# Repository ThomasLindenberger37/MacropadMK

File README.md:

# MacropadMK

MacropadMK is a 12-key macropad built around the Waveshare ESP32-S3-Zero. The
board combines a diode-isolated 4 × 3 keyboard matrix, three USB-C power-entry
options, and two general-purpose JST-SH connections in a compact design.

The PCB is intended for an accessible prototyping workflow: order bare boards,
assemble and validate the first units by hand, then reuse the same LCSC-aware
bill of materials for a later JLCPCB assembly run.

## Design overview

- Controller: ESP32-S3-Zero
- Keyboard: 12 switches arranged as 4 rows × 3 columns
- Isolation: one diode per switch
- Matrix direction: `COL2ROW`
- Supply rails: `BOARD_5V`, `3V3`, and `GND`
- USB-C inputs: the controller connector plus two alternative PCB connectors
- Expansion: two identically pinned 3-position JST-SH connectors

## Keyboard matrix

The switches form a 4-row by 3-column matrix. `ROW1` through `ROW4` are scanned
one at a time by driving the selected row low. `COL1` through `COL3` are inputs,
each held high by an external 10 kΩ pull-up resistor to `3V3`.

Each key is an independent branch:

```text
COLx -> switch -> diode anode -> diode cathode -> ROWx
```

The diode orientation is `COL2ROW`: the cathode, identified by the stripe on the
physical diode, points toward the row line. When a selected row is low and a key
on that row is pressed, its column input is pulled low through the switch and
diode.

| Signal group | Quantity | Scan role | External bias |
| --- | ---: | --- | --- |
| `ROW1`–`ROW4` | 4 | Driven low individually | None |
| `COL1`–`COL3` | 3 | Digital inputs | 10 kΩ to `3V3` per column |

## USB-C power architecture

The ESP32-S3-Zero already has its own USB-C connector. The PCB provides two
additional connector positions as alternative 5 V inputs:

- Horizontal/right-angle: HRO `TYPE-C-31-M-12`
- Vertical/axial: `MC-110LD-L124`, USB 2.0, 16 pins, with THT mounting tabs
- Vertical connector LCSC/JLCPCB part number: `C3039282`

The additional connectors are currently used only for power. They are still
full USB 2.0 connector parts so that the same components and footprints can be
reused in future designs with USB data support.

Each additional receptacle follows these connection rules:

- Tie all VBUS pins of that receptacle together.
- Connect all GND pins to board ground.
- Connect `CC1` to GND through its own 5.1 kΩ resistor.
- Connect `CC2` separately to GND through its own 5.1 kΩ resistor.
- Connect the connector shield to GND.
- Leave `D+`, `D-`, `SBU1`, and `SBU2` unconnected and mark them as no-connect.

Each alternative receptacle feeds the common `BOARD_5V` rail through a separate
solder bridge. `BOARD_5V` connects to the ESP32-S3-Zero 5 V pin. An optional
resettable fuse rated for approximately 1 A can be fitted ahead of the shared
rail.

Place 10 µF bulk capacitance and 100 nF decoupling close to the 5 V input. Route
VBUS with approximately 0.8–1.0 mm wide traces; 0.25 mm traces are not
recommended for a 1 A supply path.

> **Power-source warning:** The board does not provide input OR-ing or reverse-
> current isolation. Only one USB power source may be connected at a time unless
> suitable input decoupling and source isolation are added.

## Additional connectors

The board provides two identically pinned 3-position JST-SH connectors with a
1.0 mm pitch.

- KiCad symbol: `Connector_Generic:Conn_01x03`
- KiCad footprint:
  `Connector_JST:JST_SH_SM03B-SRSS-TB_1x03-1MP_P1.00mm_Horizontal`

| Pin | Signal |
| ---: | --- |
| 1 | `GND` |
| 2 | `3V3` |
| 3 | Signal |

## Sourcing and assembly strategy

Components should use LCSC `C` part numbers wherever practical. The same part
numbers can be used both for loose component orders from LCSC and for JLCPCB
assembly BOM matching.

The intended manufacturing sequence is:

1. Order unassembled prototype PCBs.
2. Hand-assemble and electrically validate the first boards.
3. Resolve ERC/DRC findings and confirm footprints, polarity, and connector
   mechanics.
4. Reuse the validated BOM for a later JLCPCB assembly order.

## Project assets

[Download the schematic as PDF](assets/MacropadMK-schematic.pdf).

Some connector or encoder models may be absent from the rendered 3D preview if
their STEP files are not available locally. This does not affect the Gerber or
drill exports, but mechanical fit must still be checked before ordering.

## Fabrication and documentation exports

The repository contains its KiBot automation directly under `scripts/`. Docker
is required; the scripts use the KiCad 10 KiBot image configured in
`scripts/project.config.yaml`.

Generate the schematic PDF/SVG and the 3D preview:

```bash
./scripts/assets.sh
```

Generate Gerbers, drill files, BOM, placement data, the manufacturer ZIP, and
STEP models:

```bash
./scripts/fabrication.sh
```

Generated manufacturing files are written to `Fabrication/`. The validated
manufacturer archive is `Fabrication/MacropadMK-Gerber_Pack.zip`.

The relevant configuration files are:

- `scripts/project.config.yaml` — project name, KiCad image, PCB thickness, and
  mechanical-hole settings
- `scripts/kibot/config.kibot.yaml` — manufacturing outputs and production
  layers
- `scripts/kibot/kibot_assets.kibot.yaml` — documentation PDF, SVG, and 3D
  render outputs

Always run KiCad ERC and DRC and review the generated Gerbers before submitting
an order. Successful file generation does not imply that the electrical or
mechanical design is production-ready.

## Automated fabrication build

The GitHub Actions fabrication workflow generates manufacturing artifacts when
changes are pushed to the repository:

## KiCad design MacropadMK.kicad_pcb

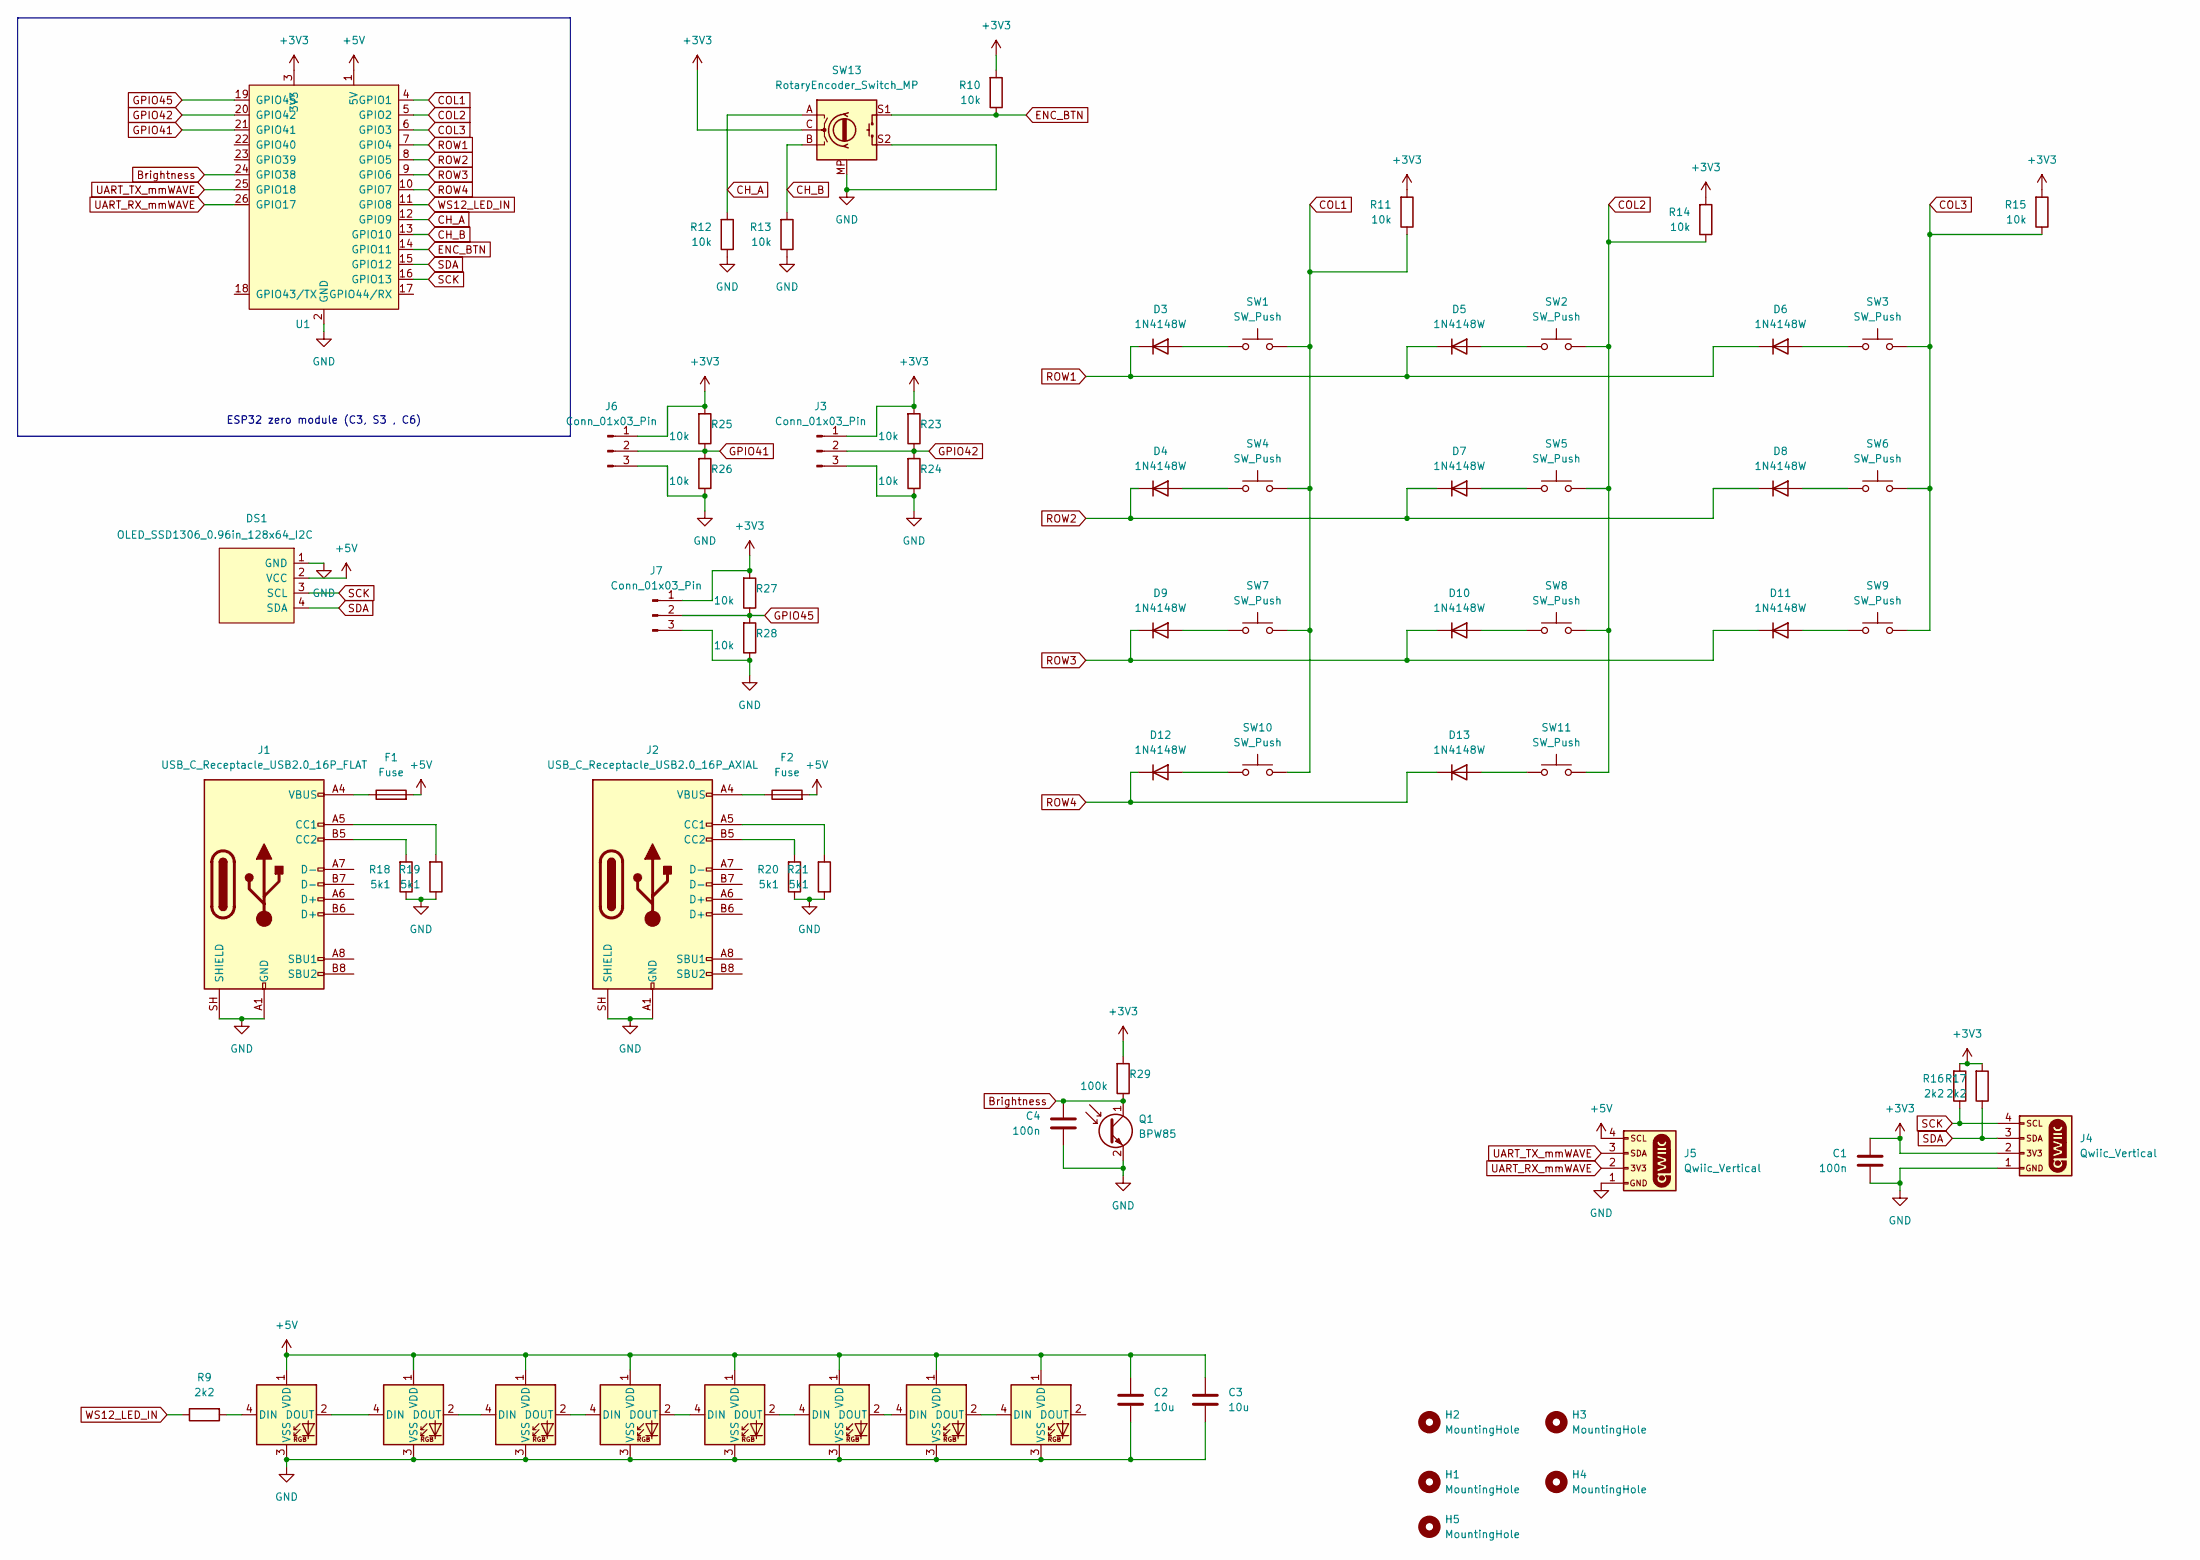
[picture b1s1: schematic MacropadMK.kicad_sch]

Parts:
C1, C4: 100n; C_0805_2012Metric; JLCPCB Part C6119867
C2, C3: 10u; C_0805_2012Metric
D1, D2, D14, D15, D16, D17, D18, D19: WS2812B; LED_WS2812B_PLCC4_5.0x5.0mm_P3.2mm; LCSC C22461793
D3, D4, D5, D6, D7, D8, D9, D10, D11, D12, D13: 1N4148W; D_SOD-123
DS1: OLED_SSD1306_0.96in_128x64_I2C
F1, F2: Fuse; Fuse_0805_2012Metric
H1, H2, H3, H4, H5: MountingHole; MountingHole_3.2mm_M3
J1: USB_C_Receptacle_USB2.0_16P_FLAT; USB_C_Receptacle_HRO_TYPE-C-31-M-12; LCSC C165948
J2: USB_C_Receptacle_USB2.0_16P_AXIAL; USB_C_Receptacle_JAE_DX07S024WJ3R400; LCSC MC-110LD-L124
J3, J6, J7: Conn_01x03_Pin; JST_SH_BM03B-SRSS-TB_1x03-1MP_P1.00mm_Vertical
J4, J5: Qwiic_Vertical; JST_SH_BM04B-SRSS-TB_1x04-1MP_P1.00mm_Vertical
Q1: BPW85; LED_0603_1608Metric
R9, R16, R17: 2k2; R_0603_1608Metric
R10, R11, R12, R13, R14, R15, R23, R24, R25, R26, R27, R28: 10k; R_0603_1608Metric
R18, R19, R20, R21: 5k1; R_0603_1608Metric
R29: 100k; R_0603_1608Metric
SW1, SW2, SW3, SW4, SW5, SW6, SW7, SW8, SW9, SW10, SW11: SW_Push; SW_Cherry_MX_PCB_1.00u
SW13: RotaryEncoder_Switch_MP; RotaryEncoder_Alps_EC11E-Switch_Vertical_H20mm
U1: ESP32-S3-Zero

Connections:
+3V3: C1.1, J3.1, J4.2, J6.1, J7.1, R10.2, R11.2, R14.2, R15.2, R16.2, R17.2, R23.2, R25.2, R27.2, R29.2, SW13.C, U1.3 (3V3)
+5V: C2.1, C3.1, D1.1 (VDD), D2.1 (VDD), D14.1 (VDD), D15.1 (VDD), D16.1 (VDD), D17.1 (VDD), D18.1 (VDD), D19.1 (VDD), DS1.2 (VCC), F1.2, F2.2, J5.4, U1.1 (5V)
Brightness: C4.1, Q1.1 (C), R29.1, U1.24 (GPIO38)
CH_A: R12.2, SW13.A, U1.12 (GPIO9)
CH_B: R13.2, SW13.B, U1.13 (GPIO10)
COL1: R11.1, SW1.2, SW4.2, SW7.2, SW10.2, U1.4 (GPIO1)
COL2: R14.1, SW2.2, SW5.2, SW8.2, SW11.2, U1.5 (GPIO2)
COL3: R15.1, SW3.2, SW6.2, SW9.2, U1.6 (GPIO3)
ENC_BTN: R10.1, SW13.S1, U1.14 (GPIO11)
GND: C1.2, C2.2, C3.2, C4.2, D1.3 (VSS), D2.3 (VSS), D14.3 (VSS), D15.3 (VSS), D16.3 (VSS), D17.3 (VSS), D18.3 (VSS), D19.3 (VSS), DS1.1 (GND), J1.A1 (GND), J1.A12 (GND), J1.B1 (GND), J1.B12 (GND), J1.SH (SHIELD), J2.A1 (GND), J2.A12 (GND), J2.B1 (GND), J2.B12 (GND), J2.SH (SHIELD), J3.3, J4.1, J5.1, J6.3, J7.3, Q1.2 (E), R12.1, R13.1, R18.1, R19.1, R20.1, R21.1, R24.1, R26.1, R28.1, SW13.MP, SW13.S2, U1.2 (GND)
GPIO41: J6.2, R25.1, R26.2, U1.21 (GPIO41)
GPIO42: J3.2, R23.1, R24.2, U1.20 (GPIO42)
GPIO45: J7.2, R27.1, R28.2, U1.19 (GPIO45)
unnamed: D1.4 (DIN), R9.2
unnamed: D1.2 (DOUT), D2.4 (DIN)
unnamed: D3.2 (A), SW1.1
unnamed: D4.2 (A), SW4.1
unnamed: D5.2 (A), SW2.1
unnamed: D6.2 (A), SW3.1
unnamed: D7.2 (A), SW5.1
unnamed: D8.2 (A), SW6.1
unnamed: D9.2 (A), SW7.1
unnamed: D10.2 (A), SW8.1
unnamed: D11.2 (A), SW9.1
unnamed: D12.2 (A), SW10.1
unnamed: D13.2 (A), SW11.1
unnamed: D2.2 (DOUT), D14.4 (DIN)
unnamed: D14.2 (DOUT), D15.4 (DIN)
unnamed: D15.2 (DOUT), D16.4 (DIN)
unnamed: D16.2 (DOUT), D17.4 (DIN)
unnamed: D17.2 (DOUT), D18.4 (DIN)
unnamed: D18.2 (DOUT), D19.4 (DIN)
unnamed: F1.1, J1.A4 (VBUS), J1.A9 (VBUS), J1.B4 (VBUS), J1.B9 (VBUS)
unnamed: F2.1, J2.A4 (VBUS), J2.A9 (VBUS), J2.B4 (VBUS), J2.B9 (VBUS)
unnamed: J1.A5 (CC1), R19.2
unnamed: J1.B5 (CC2), R18.2
unnamed: J2.A5 (CC1), R21.2
unnamed: J2.B5 (CC2), R20.2
ROW1: D3.1 (K), D5.1 (K), D6.1 (K), U1.7 (GPIO4)
ROW2: D4.1 (K), D7.1 (K), D8.1 (K), U1.8 (GPIO5)
ROW3: D9.1 (K), D10.1 (K), D11.1 (K), U1.9 (GPIO6)
ROW4: D12.1 (K), D13.1 (K), U1.10 (GPIO7)
SCK: DS1.3 (SCL), J4.4, R16.1, U1.16 (GPIO13)
SDA: DS1.4 (SDA), J4.3, R17.1, U1.15 (GPIO12)
UART_RX_mmWAVE: J5.2, U1.26 (GPIO17)
UART_TX_mmWAVE: J5.3, U1.25 (GPIO18)
WS12_LED_IN: R9.1, U1.11 (GPIO8)

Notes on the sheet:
ESP32 zero module (C3, S3 , C6)

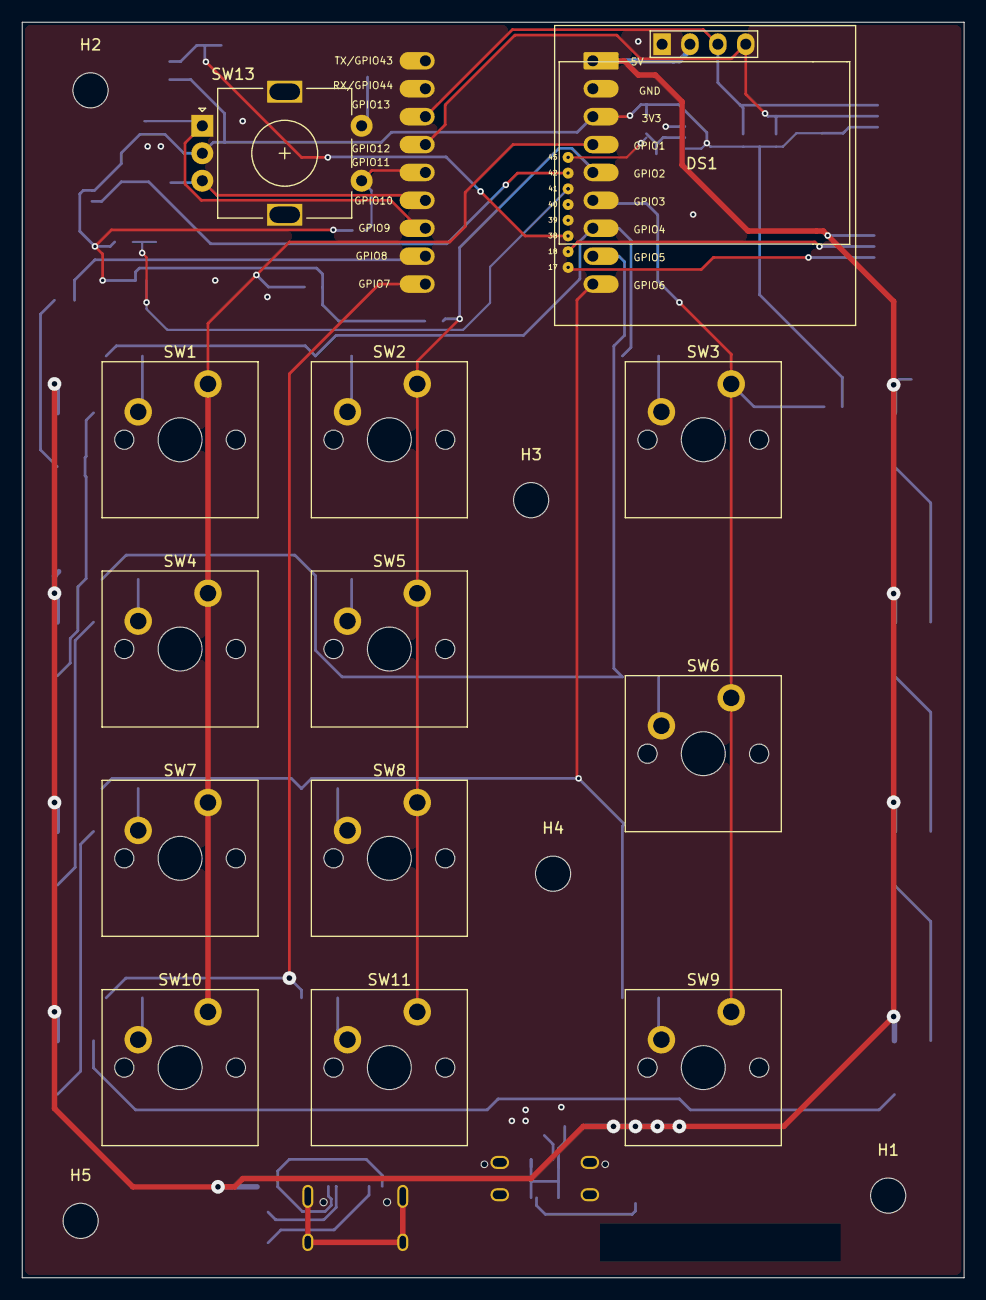
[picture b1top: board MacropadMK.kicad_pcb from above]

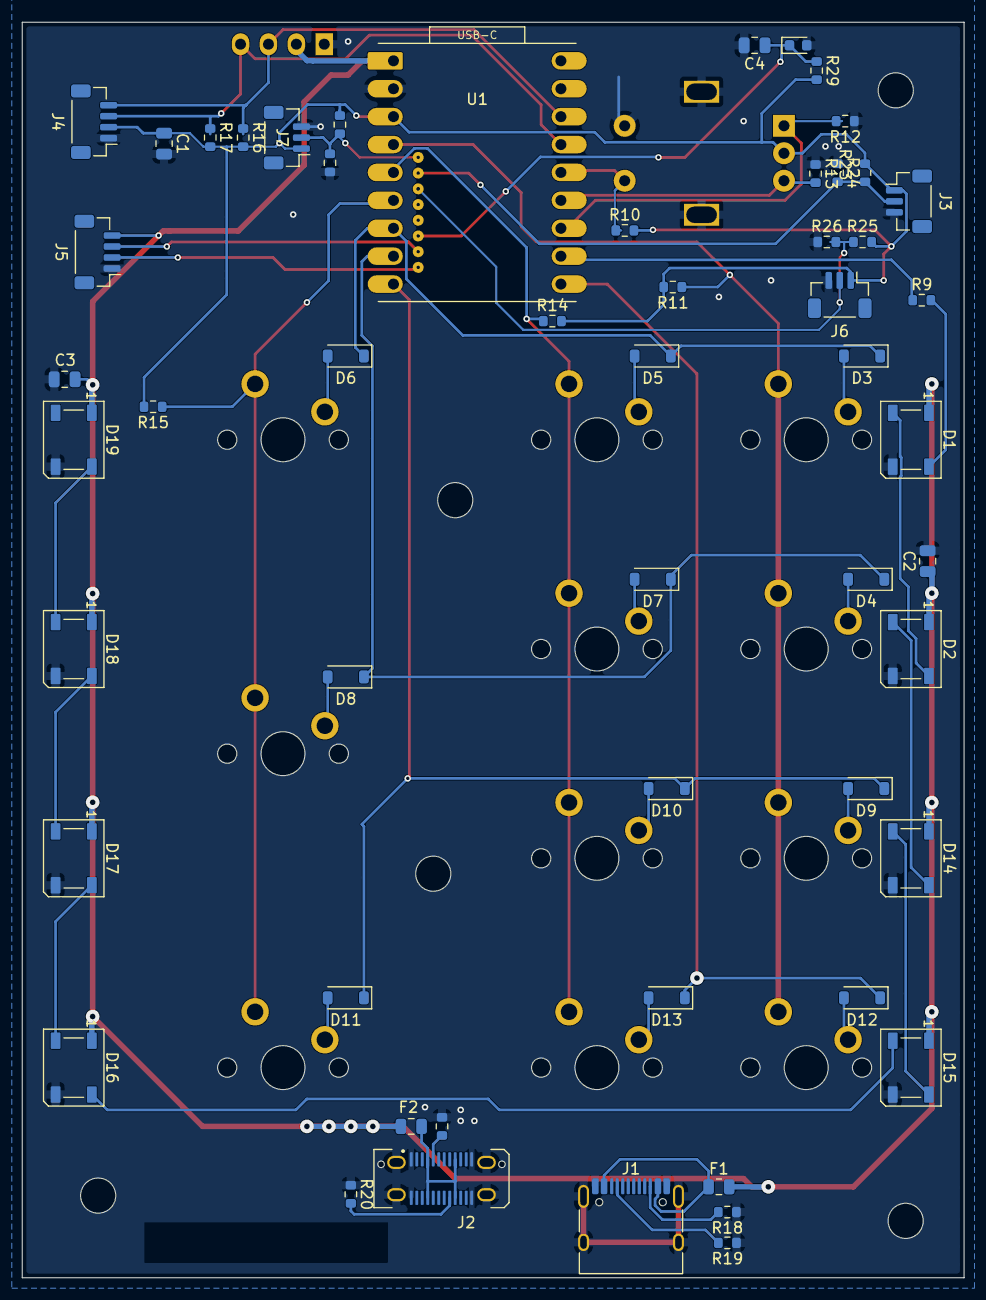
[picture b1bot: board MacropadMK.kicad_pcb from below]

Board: 2 copper layers, 85.7 x 114.3 mm, 72 parts (54 on the bottom side), 47 nets.
